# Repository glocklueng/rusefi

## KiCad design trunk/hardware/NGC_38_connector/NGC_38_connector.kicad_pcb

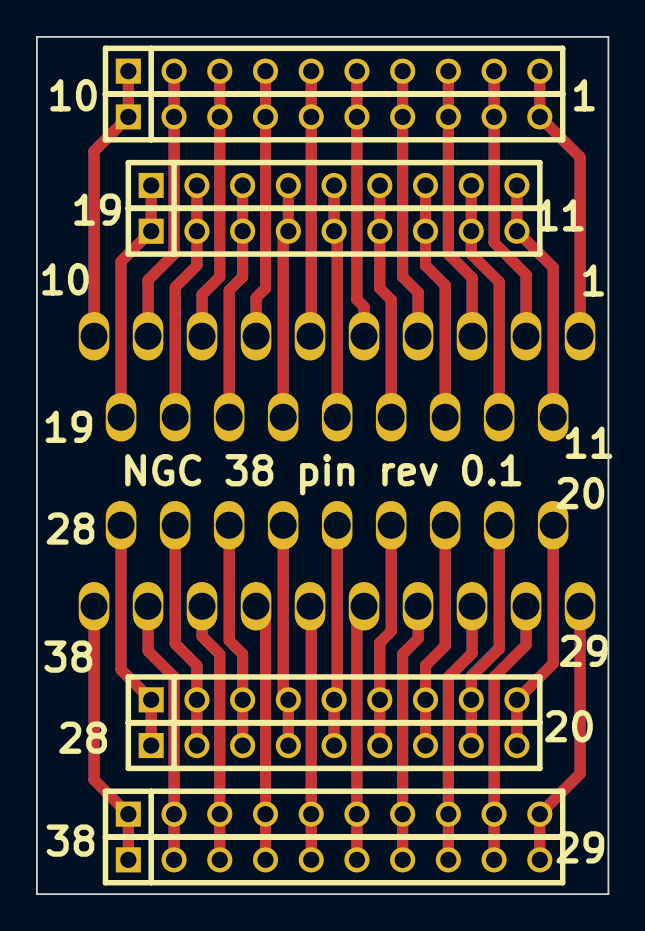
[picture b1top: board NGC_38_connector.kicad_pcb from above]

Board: 2 copper layers, 31.8 x 47.6 mm, 9 parts (0 on the bottom side), 38 nets.

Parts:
P1: DIL38; PCM_C1
P2, P4, P6, P9: CONN_10; SIL-10
P3, P5, P7, P8: CONN_9; SIL-9

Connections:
unnamed: P1.1, P2.1, P6.1
unnamed: P1.2, P2.2, P6.2
unnamed: P1.3, P2.3, P6.3
unnamed: P1.4, P2.4, P6.4
unnamed: P1.5, P2.5, P6.5
unnamed: P1.6, P2.6, P6.6
unnamed: P1.7, P2.7, P6.7
unnamed: P1.8, P2.8, P6.8
unnamed: P1.9, P2.9, P6.9
unnamed: P1.10, P2.10, P6.10
unnamed: P1.17, P3.7, P7.7
unnamed: P1.24, P5.5, P8.5
unnamed: P1.25, P5.6, P8.6
unnamed: P1.26, P5.7, P8.7
unnamed: P1.27, P5.8, P8.8
unnamed: P1.28, P5.9, P8.9
unnamed: P1.11, P3.1, P7.1
unnamed: P1.12, P3.2, P7.2
unnamed: P1.13, P3.3, P7.3
unnamed: P1.14, P3.4, P7.4
unnamed: P1.15, P3.5, P7.5
unnamed: P1.16, P3.6, P7.6
unnamed: P1.23, P5.4, P8.4
unnamed: P1.18, P3.8, P7.8
unnamed: P1.19, P3.9, P7.9
unnamed: P1.31, P4.3, P9.3
unnamed: P1.29, P4.1, P9.1
unnamed: P1.30, P4.2, P9.2
unnamed: P1.32, P4.4, P9.4
unnamed: P1.33, P4.5, P9.5
unnamed: P1.34, P4.6, P9.6
unnamed: P1.35, P4.7, P9.7
unnamed: P1.36, P4.8, P9.8
unnamed: P1.37, P4.9, P9.9
unnamed: P1.38, P4.10, P9.10
unnamed: P1.20, P5.1, P8.1
unnamed: P1.21, P5.2, P8.2
unnamed: P1.22, P5.3, P8.3

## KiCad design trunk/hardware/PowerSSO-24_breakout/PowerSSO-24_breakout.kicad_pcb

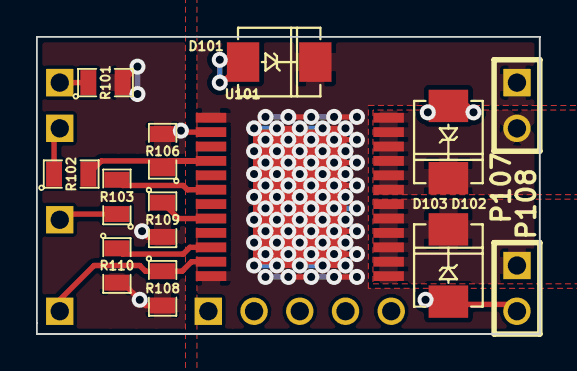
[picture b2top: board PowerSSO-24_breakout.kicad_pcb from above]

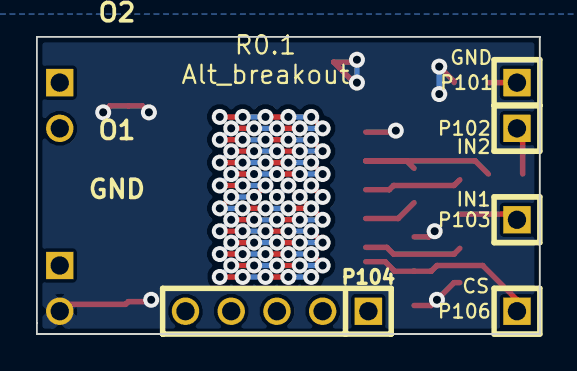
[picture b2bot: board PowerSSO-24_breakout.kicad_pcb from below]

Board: 2 copper layers, 27.9 x 16.5 mm, 18 parts (5 on the bottom side), 12 nets.

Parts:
D101, D102, D103: P6SMB36AT3G; DO-214AA(SMB)
P101, P102, P103, P106: CONN_1; SIL-1
P104: CONN_5; SIL-5
P107, P108: CONN_2; SIL-2
R101: TBD; SM0805
R102, R103, R106, R108: 10K; SM0805
R109, R110: 1K; SM0805
U101: VND5E025AKTR; PowerSSO-24

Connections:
/CS_DIS: P106.1, R108.1, U101.11
/I1: R109.1, U101.8
/I2: R110.1, U101.10
/IN1: R103.2, U101.6
/IN2: R102.2, R106.1, U101.4
/O1: D103.2, P108.1, U101.13, U101.14, U101.15, U101.16, U101.17, U101.18
/O2: D102.2, P107.2, U101.19, U101.20, U101.21, U101.22, U101.23, U101.24
/VCC: D101.2, P107.1, U101.1, U101.12, U101.EXP
GND: D101.1, D102.1, D103.1, P108.2, R101.2, R106.2, R108.2, R109.2, R110.2, U101.2
unnamed: P101.1, R101.1
unnamed: P103.1, R103.1
unnamed: P102.1, R102.1

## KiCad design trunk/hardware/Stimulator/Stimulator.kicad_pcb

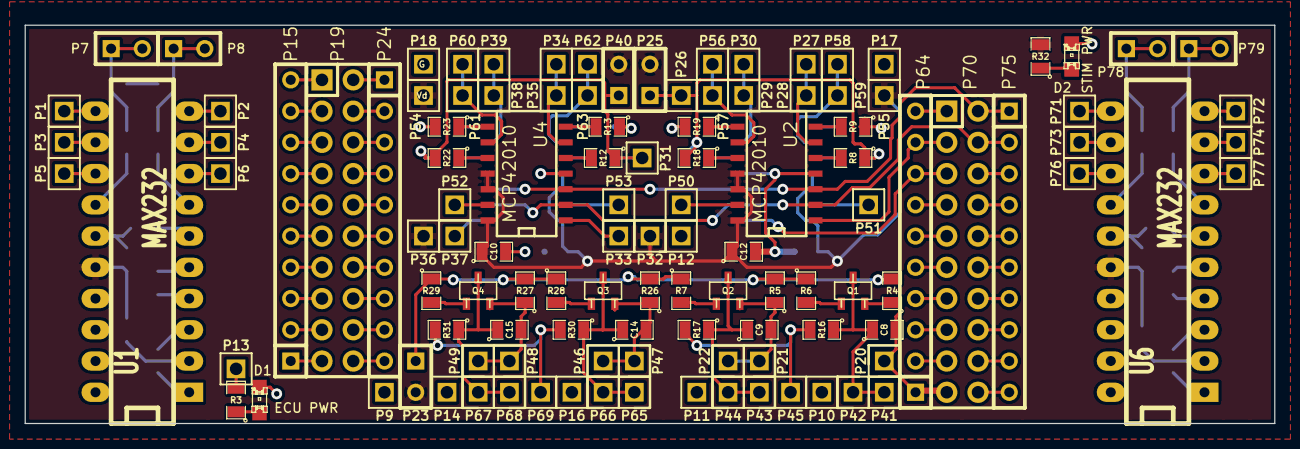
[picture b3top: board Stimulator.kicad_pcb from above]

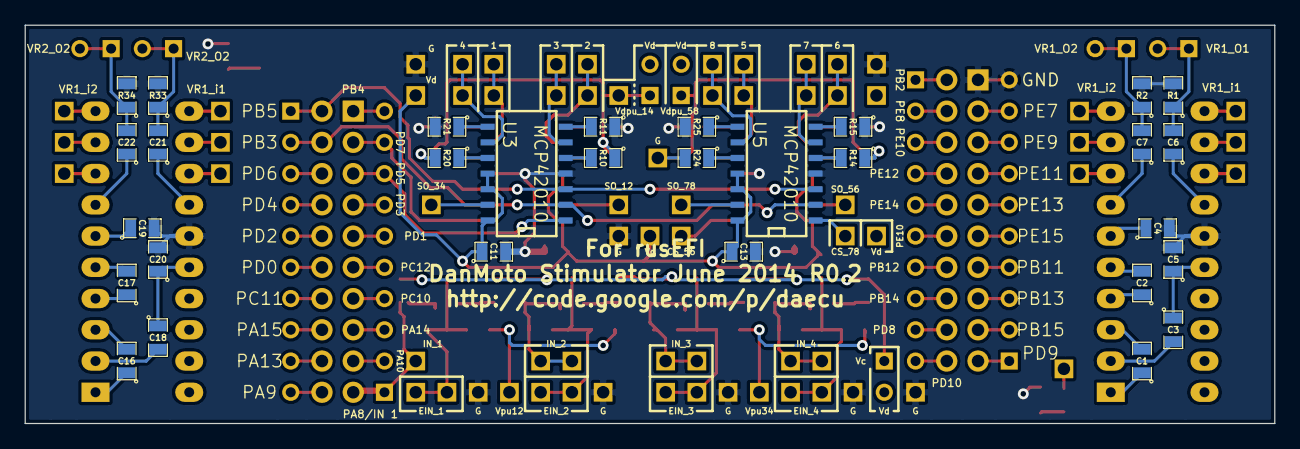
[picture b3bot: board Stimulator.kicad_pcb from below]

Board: 2 copper layers, 101.6 x 32.4 mm, 147 parts (30 on the bottom side), 122 nets.

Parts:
C1, C2, C3, C4, C5, C6, C7, C16, C17, C18, C19, C20, C21, C22: 1uF; SM0805
C8, C9, C14, C15: 100 pF; SM0805
C10, C11, C12, C13: 0.1uF; SM0805
D1: ECU PWR; LED-0805
D2: STIM PWR; LED-0805
P1, P2, P3, P4, P5, P6, P9, P10, P11, P12, P13, P14, P16, P17, P18, P20, P21, P22, P26, P27, P28, P29, P30, P31, P32, P33, P34, P35, P36, P37, P38, P39, P41, P42, P43, P44, P45, P46, P47, P48, P49, P50, P51, P52, P53, P54, P55, P56, P57, P58, P59, P60, P61, P62, P63, P65, P66, P67, P68, P69, P71, P72, P73, P74, P76, P77: CONN_1; PIN_ARRAY_1
P7, P8, P23, P25, P40, P78, P79: TEST; SIL-2
P15, P24, P64, P75: CONN_10; SIL-10
P19, P70: CONN_10X2; Pin_Header_Straight_2x10
Q1, Q2, Q3, Q4: 2N7002; sot23
R1, R2, R4, R5, R6, R7, R16, R17, R26, R27, R28, R29, R30, R31, R33, R34: 10k; SM0805
R3, R32: 700R; SM0805
R8, R9, R10, R11, R12, R13, R14, R15, R18, R19, R20, R21, R22, R23, R24, R25: 0; SM0805
U1, U6: MAX232; DIP-20__300_ELL
U2, U3, U4, U5: MCP42010; SO14N

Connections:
/CS_12: P64.9, P70.3, U2.1
/CS_34: P64.8, P70.5, U3.1
/CS_56: P33.1, U4.1
/CS_78: P37.1, U5.1
/EIN_1: C8.1, P41.1, P42.1, Q1.2, R16.1
/EIN_2: C9.1, P43.1, P44.1, Q2.2, R17.1
/EIN_3: C14.1, P65.1, P66.1, Q3.2, R30.1
/EIN_4: C15.1, P67.1, P68.1, Q4.2, R31.1
/IN_1: C8.2, P20.1, P64.1, P70.19, Q1.3, R4.1
/IN_2: C9.2, P21.1, P22.1, Q2.3, R5.1
/IN_3: C14.2, P46.1, P47.1, Q3.3, R26.1
/IN_4: C15.2, P48.1, P49.1, Q4.3, R27.1
/MISO: P64.10, P70.1
/MOSI: P70.2, P75.1, U2.3, U3.3, U4.3, U5.3
/OUT1: P27.1, P28.1, U2.6
/OUT2: P56.1, P57.1, U2.9
/OUT3: P29.1, P30.1, U3.6
/OUT4: P58.1, P59.1, U3.9
/OUT5: P34.1, P35.1, U4.6
/OUT6: P60.1, P61.1, U4.9
/OUT7: P38.1, P39.1, U5.6
/OUT8: P62.1, P63.1, U5.9
/SCK: P70.4, P75.2, U2.2, U3.2, U4.2, U5.2
/VR1-O1: C6.2, P7.1, P7.2, R1.1
/VR1-O2: C7.2, P8.1, P8.2, R2.1
/VR1_i1: P1.1, U1.11
/VR1_i2: P2.1, U1.10
/VR2-O1: C21.2, P78.1, P78.2, R33.1
/VR2-O2: C22.2, P79.1, P79.2, R34.1
/VR2_i1: P71.1, U6.11
/VR2_i2: P72.1, U6.10
/Vc: P23.1, R4.2, R5.2, R6.1, R7.1, R26.2, R27.2, R28.1, R29.1
/Vd: C3.1, C5.1, C10.1, C11.1, C12.1, C13.1, C18.1, C20.1, P23.2, P25.2, P32.1, P36.1, P40.2, P54.1, P55.1, R32.2, U1.16, U2.11, U2.12, U2.14, U3.11, U3.12, U3.14, U4.11, U4.12, U4.14, U5.11, U5.12, U5.14, U6.16
/Vdpu_14: P25.1, P26.1, R8.1, R10.1, R18.2, R20.2
/Vdpu_58: P31.1, P40.1, R12.1, R14.1, R22.2, R24.2
/Vipu12: P45.1, R16.2, R17.2
/Vipu34: P69.1, R30.2, R31.2
GND: C4.2, C5.2, C10.2, C11.2, C12.2, C13.2, C19.2, C20.2, D1.2, D2.2, P9.1, P10.1, P11.1, P12.1, P14.1, P15.10, P16.1, P17.1, P18.1, P19.1, R1.2, R2.2, R9.1, R11.1, R13.1, R15.1, R19.2, R21.2, R23.2, R25.2, R33.2, R34.2, U1.15, U2.4, U3.4, U4.4, U5.4, U6.15
unnamed: P53.1, U5.13
unnamed: P70.16, P75.8
unnamed: P15.6, P19.9
unnamed: P15.7, P19.7
unnamed: P15.8, P19.5
unnamed: P15.9, P19.3
unnamed: P70.6, P75.3
unnamed: P70.8, P75.4
unnamed: P70.10, P75.5
unnamed: P70.12, P75.6
unnamed: P70.14, P75.7
unnamed: P15.5, P19.11
unnamed: P70.18, P75.9
unnamed: P70.20, P75.10
unnamed: P64.2, P70.17
unnamed: P64.3, P70.15
unnamed: P64.4, P70.13
unnamed: P64.5, P70.11
unnamed: P64.6, P70.9
unnamed: P64.7, P70.7
unnamed: P19.6, P24.3
unnamed: P19.2, P24.1
unnamed: P19.4, P24.2
unnamed: P19.8, P24.4
unnamed: P19.10, P24.5
unnamed: P19.12, P24.6
unnamed: P19.14, P24.7
unnamed: P19.16, P24.8
unnamed: P19.18, P24.9
unnamed: P19.20, P24.10
unnamed: P15.1, P19.19
unnamed: P15.2, P19.17
unnamed: P15.3, P19.15
unnamed: P15.4, P19.13
unnamed: R14.2, U5.5
unnamed: R15.2, U5.7
unnamed: R25.1, U5.8
unnamed: R24.1, U5.10
unnamed: P50.1, U2.13
unnamed: P52.1, U4.13
unnamed: P51.1, U3.13
unnamed: C16.1, U6.1
unnamed: C16.2, U6.3
unnamed: C17.1, U6.4
unnamed: C17.2, U6.5
unnamed: C18.2, U6.2
unnamed: C19.1, U6.6
unnamed: P77.1, U6.8
unnamed: P76.1, U6.13
unnamed: D2.1, R32.1
unnamed: P13.1, R3.2
unnamed: C22.1, U6.7
unnamed: P74.1, U6.9
unnamed: P73.1, U6.12
unnamed: C21.1, U6.14
unnamed: P3.1, U1.12
unnamed: P4.1, U1.9
unnamed: C7.1, U1.7
unnamed: C1.1, U1.1
unnamed: C3.2, U1.2
unnamed: C1.2, U1.3
unnamed: C2.1, U1.4
unnamed: C2.2, U1.5
unnamed: C4.1, U1.6
unnamed: P6.1, U1.8
unnamed: P5.1, U1.13
unnamed: C6.1, U1.14
unnamed: D1.1, R3.1
unnamed: Q1.1, R6.2
unnamed: R8.2, U2.5
unnamed: R9.2, U2.7
unnamed: R19.1, U2.8
unnamed: R18.1, U2.10
unnamed: Q2.1, R7.2
unnamed: Q3.1, R28.2
unnamed: Q4.1, R29.2
unnamed: R13.2, U4.7
unnamed: R23.1, U4.8
unnamed: R22.1, U4.10
unnamed: R10.2, U3.5
unnamed: R11.2, U3.7
unnamed: R21.1, U3.8
unnamed: R20.1, U3.10
unnamed: R12.2, U4.5

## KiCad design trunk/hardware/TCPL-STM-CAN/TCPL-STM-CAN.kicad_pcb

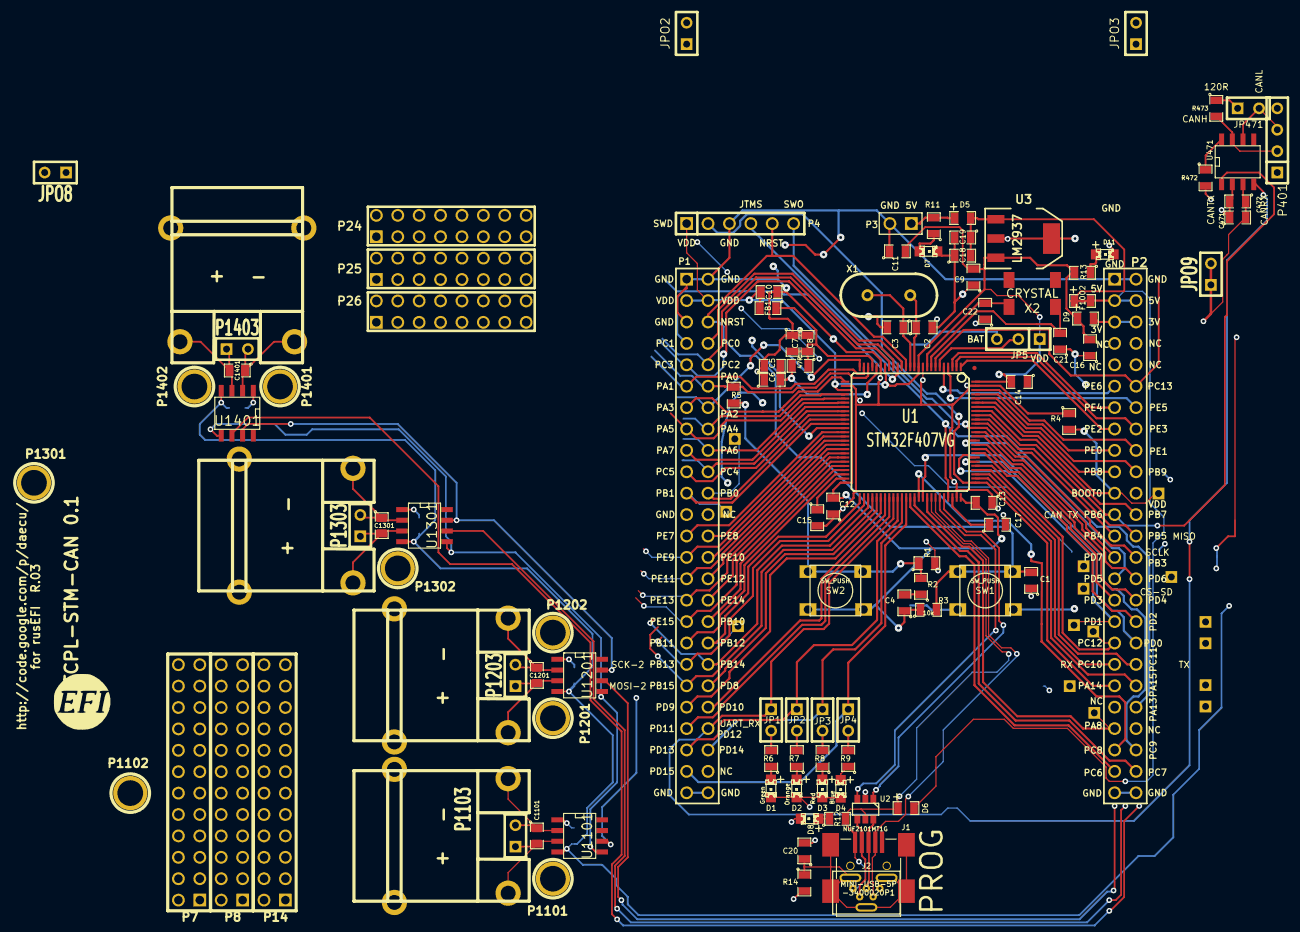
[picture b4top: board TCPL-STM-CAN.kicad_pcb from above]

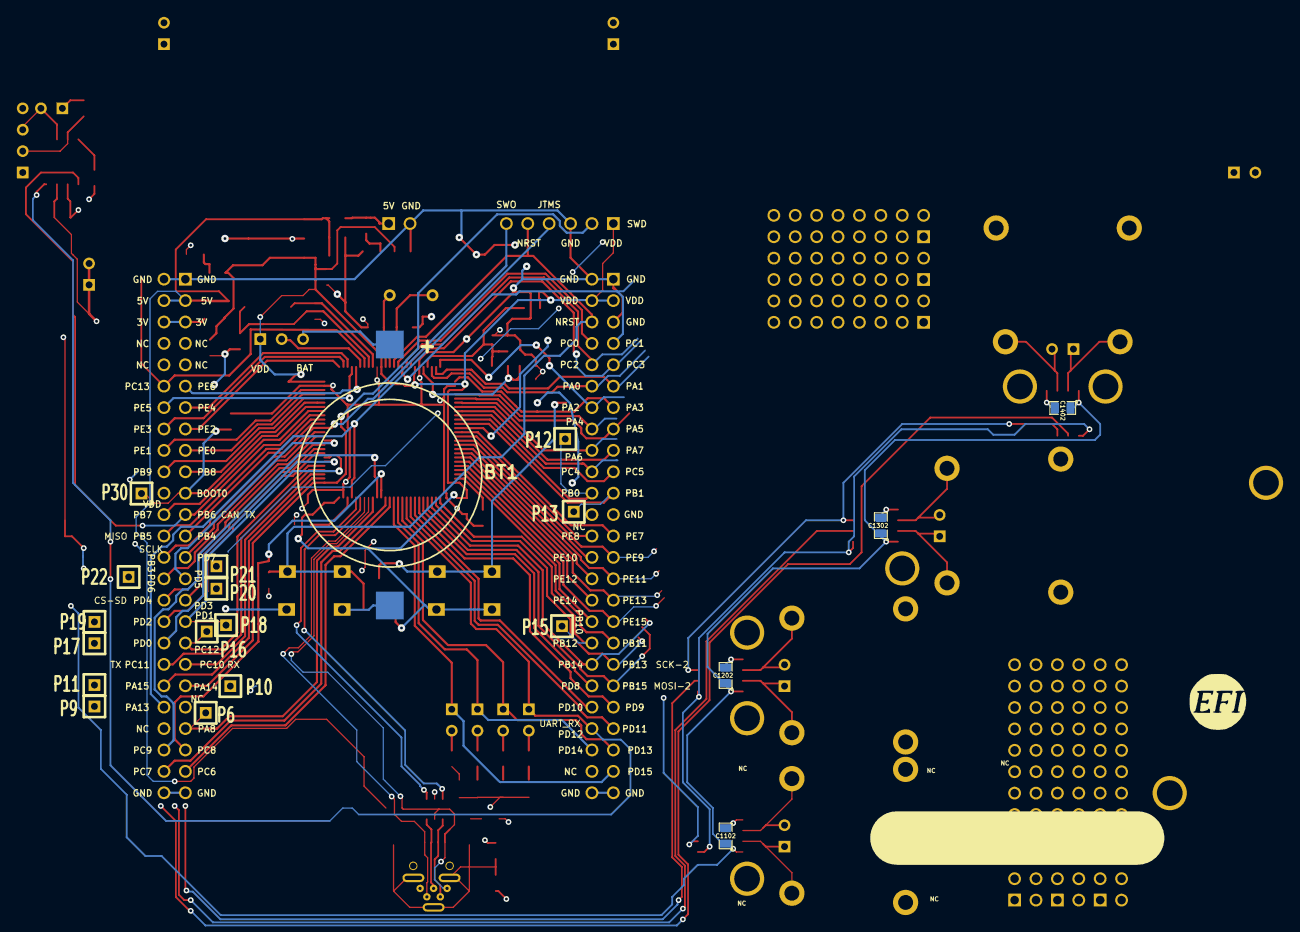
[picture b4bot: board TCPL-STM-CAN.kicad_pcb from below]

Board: 4 copper layers, 129 parts (21 on the bottom side), 124 nets.

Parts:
BT1: BATTERY_CR2032; BATT_CR2032_MPD
C1, C5, C8: 0.01uF; SM0805
C2, C3: 20pF; SM0805
C4, C15, C17: 2u2F; SM0805
C6, C7, C16: 1uF; SM0805
C9, C10, C11, C12, C13, C14, C18, C20, C471: 0.1uF; SM0805
C19, C472: 4.7uF; SM0805
C21, C22: 12.5pF; SM0805
C1101, C1201, C1301, C1401: 10nF; SM0805-SM0603
C1102, C1202, C1302, C1402: 100nF; SM0805-SM0603
D1, D7, D8, D11: LED-grn; LED-0805_A
D2: LED-org; LED-0805_A
D3: LED-red; LED-0805_A
D4: LED-blu; LED-0805_A
D5, D6, D9: DIODESCH; SM0805-diode
F1002: FUSE; SM0805-diode
FB1: FILTER; SM0805
G1: LOGO; LOGO_F
G2: LOGO
J1: MINI-USB-5P-3400020P1
J2: MINI-USB-5P-3400020P1V; MINI-USB_RCTP_V-T_B
JP1, JP2, JP3, JP4, JP471: JUMPER; JUMPER-2
JP5: JUMPER3; SIL-3
JPO2, JPO3, JPO8, JPO9: TEST-gnd; SIL-2
P1, P2: CONN_25X2; PIN_ARRAY_25x2_A
P3: CONN_2; PIN_ARRAY_2_A
P4: CONN_6; PIN_ARRAY-6X1
P6, P9, P10, P11, P12, P13, P15, P16, P17, P18, P19, P20, P21, P22, P30: CONN_1; SIL-1
P7, P8, P14: CONN_12X2; pin_array_12x2
P24, P25, P26: CONN_8X2; pin_array_8x2
P401: CONN_4; SIL-4
P1101, P1102, P1201, P1202, P1301, P1302, P1401, P1402: CONN_1; 1pin
P1103, P1203, P1303, P1403: CONN_2; SIL-2
P1104, P1204, P1304, P1404: CONN_2; tcpl_PCC-SMP
R1, R3, R4, R472: 10k; SM0805
R2: 100R; SM0805
R5: 330R; SM0805
R6, R7, R8, R9: 680R; SM0805
R10: 47R; SM0805
R11, R12, R13: 1k; SM0805
R14: 100k; SM0805
R473: 120; SM0805
SW1, SW2: SW_PUSH; TL-1105
U1: STM32F407VG; TQFP_100
U2: NUF2101MT1G; SOT-457
U3: LM2937; SOT223
U471: SN65HVD230; SO8E
U1101, U1201, U1301, U1401: MAX31855KASA; SO8E
X1: CRYSTAL; HC-49V
X2: CRYSTAL; MC-306

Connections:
/can_brd_1/3.3V: C471.2, C472.1, C1102.1, C1202.1, C1302.1, C1402.1, D9.2, JPO9.1, JPO9.2, P2.5, P2.6, U471.3, U1101.4, U1201.4, U1301.4, U1401.4
/can_brd_1/5V: C18.2, C19.1, D5.2, D6.2, F1002.1, F1002.2, JPO8.1, JPO8.2, P2.3, P2.4, P401.1, U3.1
/can_brd_1/CANH: P401.2, R473.2, U471.7
/can_brd_1/CANL: JP471.2, P401.3, U471.6
/can_brd_1/CAN_RX: JP1.1, P1.44, U1.59, U471.4
/can_brd_1/CAN_TX: P2.23, U1.92, U471.1
/stm32f407_board/BOOT0: P2.21, P30.1, R4.2, U1.94
/stm32f407_board/D+: J1.3, J2.3, U2.6
/stm32f407_board/D-: J1.2, J2.2, U2.4
/stm32f407_board/NRST: C1.2, P1.6, P4.5, R3.2, SW1.1, U1.14
/stm32f407_board/PA0: P1.12, R5.1, U1.23
/stm32f407_board/PA1: P1.11, U1.24
/stm32f407_board/PA2: P1.14, U1.25
/stm32f407_board/PA3: P1.13, U1.26
/stm32f407_board/PA4: P1.16, U1.29
/stm32f407_board/PA5: P1.15, U1.30
/stm32f407_board/PA6: P1.18, U1.31
/stm32f407_board/PA7: P1.17, U1.32
/stm32f407_board/PA9: D6.1, J1.1, J2.1, R12.2, U1.68, U2.5
/stm32f407_board/PA10: J1.4, J2.4, U1.69
/stm32f407_board/PA11: U1.70, U2.3
/stm32f407_board/PA12: U1.71, U2.1
/stm32f407_board/PA15: P2.40, P11.1, U1.77
/stm32f407_board/PB0: P1.22, P12.1, U1.35
/stm32f407_board/PB1: P1.21, P13.1, U1.36
/stm32f407_board/PB3: P2.28, P4.6, U1.89
/stm32f407_board/PB4: P2.25, U1.90
/stm32f407_board/PB5: P2.26, U1.91
/stm32f407_board/PB7: P2.24, U1.93
/stm32f407_board/PB8: P2.19, U1.95
/stm32f407_board/PB9: P2.20, U1.96
/stm32f407_board/PB10: P1.34, U1.47
/stm32f407_board/PB11: P1.35, U1.48
/stm32f407_board/PB13: P1.37, U1.52
/stm32f407_board/PB14: P1.38, U1.53
/stm32f407_board/PB15: P1.39, U1.54
/stm32f407_board/PC0: P1.8, U1.15
/stm32f407_board/PC1: P1.7, U1.16
/stm32f407_board/PC2: P1.10, U1.17
/stm32f407_board/PC3: P1.9, U1.18
/stm32f407_board/PC4: P1.20, U1.33
/stm32f407_board/PC5: P1.19, U1.34
/stm32f407_board/PC6: P2.47, U1.63
/stm32f407_board/PC7: P2.48, U1.64
/stm32f407_board/PC8: P2.45, U1.65
/stm32f407_board/PC9: P2.46, U1.66
/stm32f407_board/PC10: P2.37, U1.78
/stm32f407_board/PC11: P2.38, U1.79
/stm32f407_board/PC12: P2.35, P16.1, U1.80
/stm32f407_board/PC13: P2.12, U1.7
/stm32f407_board/PD0: P2.36, P17.1, U1.81
/stm32f407_board/PD1: P2.33, P18.1, U1.82
/stm32f407_board/PD2: P2.34, P19.1, U1.83
/stm32f407_board/PD3: P2.31, P20.1, U1.84
/stm32f407_board/PD4: P2.32, U1.85
/stm32f407_board/PD5: P2.29, P21.1, U1.86
/stm32f407_board/PD6: P2.30, P22.1, U1.87
/stm32f407_board/PD7: P2.27, U1.88
/stm32f407_board/PD8: P1.40, U1.55
/stm32f407_board/PD9: P1.41, U1.56
/stm32f407_board/PD10: P1.42, U1.57
/stm32f407_board/PD11: P1.43, U1.58
/stm32f407_board/PD13: JP2.1, P1.45, U1.60
/stm32f407_board/PD14: JP3.1, P1.46, U1.61
/stm32f407_board/PD15: JP4.1, P1.47, U1.62
/stm32f407_board/PE0: P2.17, U1.97
/stm32f407_board/PE1: P2.18, U1.98
/stm32f407_board/PE2: P2.15, U1.1
/stm32f407_board/PE3: P2.16, U1.2
/stm32f407_board/PE4: P2.13, U1.3
/stm32f407_board/PE5: P2.14, U1.4
/stm32f407_board/PE6: P2.11, U1.5
/stm32f407_board/PE7: P1.25, U1.38
/stm32f407_board/PE8: P1.26, U1.39
/stm32f407_board/PE9: P1.27, U1.40
/stm32f407_board/PE10: P1.28, U1.41
/stm32f407_board/PE11: P1.29, U1.42
/stm32f407_board/PE12: P1.30, U1.43
/stm32f407_board/PE13: P1.31, U1.44
/stm32f407_board/PE14: P1.32, U1.45
/stm32f407_board/PE15: P1.33, U1.46
/stm32f407_board/VDD: C4.1, C9.2, C10.2, C11.2, C12.2, C13.2, C14.2, C16.2, D9.1, FB1.2, JP5.1, P1.3, P1.4, P4.1, R3.1, R13.2, SW2.2, U1.11, U1.19, U1.28, U1.50, U1.75, U1.100, U3.3
/stm32f407_board/shield: C20.1, J1.6, J2.6, R14.1
/thermocouple1//CS: P1.36, P15.1, U1.51, U1101.6
/thermocouple1/MISO: U1101.7, U1201.7, U1301.7, U1401.7
/thermocouple1/SCK: U1101.5, U1201.5, U1301.5, U1401.5
/thermocouple1/TCPL+: C1101.2, P1103.1, P1104.2, U1101.3
/thermocouple1/TCPL-: C1101.1, P1103.2, P1104.1, U1101.2
/thermocouple2//CS: P2.39, P4.2, P10.1, U1.76, U1201.6
/thermocouple2/TCPL+: C1201.2, P1203.1, P1204.2, U1201.3
/thermocouple2/TCPL-: C1201.1, P1203.2, P1204.1, U1201.2
/thermocouple3//CS: P2.43, P6.1, U1.67, U1301.6
/thermocouple3/TCPL+: C1301.2, P1303.1, P1304.2, U1301.3
/thermocouple3/TCPL-: C1301.1, P1303.2, P1304.1, U1301.2
/thermocouple4//CS: P2.42, P4.4, P9.1, U1.72, U1401.6
/thermocouple4/TCPL+: C1401.2, P1403.1, P1404.2, U1401.3
/thermocouple4/TCPL-: C1401.1, P1403.2, P1404.1, U1401.2
GND: BT1.2, C1.1, C2.2, C3.2, C5.1, C6.1, C7.1, C8.1, C9.1, C10.1, C11.1, C12.1, C13.1, C14.1, C15.2, C16.1, C17.2, C18.1, C19.2, C20.2, C21.1, C22.1, C471.1, C472.2, C1102.2, C1202.2, C1302.2, C1402.2, D1.2, D2.2, D3.2, D4.2, D7.2, D8.2, D11.2, J1.5, J2.5, JPO2.1, JPO2.2, JPO3.1, JPO3.2, P1.1, P1.2, P1.5, P1.23, P1.49, P1.50, P2.1, P2.2, P2.49, P2.50, P3.2, P4.3, P401.4, R1.2, R4.1, R14.2, R472.2, SW1.2, U1.10, U1.20, U1.27, U1.37, U1.74, U1.99, U2.2, U3.2, U3.4, U471.2, U1101.1, U1201.1, U1301.1, U1401.1
unnamed: R472.1, U471.8
unnamed: JP471.1, R473.1
unnamed: C22.2, U1.9, X2.1
unnamed: C21.2, U1.8, X2.2
unnamed: C2.1, U1.12, X1.2
unnamed: D2.1, R7.1
unnamed: D3.1, R8.1
unnamed: D4.1, R9.1
unnamed: D7.1, R11.1
unnamed: D8.1, R12.1
unnamed: D11.1, R13.1
unnamed: D1.1, R6.1
unnamed: D5.1, P3.1, R11.2
unnamed: BT1.1, JP5.3
unnamed: JP5.2, U1.6
unnamed: JP4.2, R9.2
unnamed: JP3.2, R8.2
unnamed: JP2.2, R7.2
unnamed: JP1.2, R6.2
unnamed: R1.1, R2.2, R5.2, SW2.1
unnamed: C5.2, C6.2, R10.2, U1.21
unnamed: C3.1, U1.13, X1.1
unnamed: C17.1, U1.73
unnamed: C15.1, U1.49
unnamed: C4.2, R2.1
unnamed: C7.2, C8.2, FB1.1, R10.1, U1.22

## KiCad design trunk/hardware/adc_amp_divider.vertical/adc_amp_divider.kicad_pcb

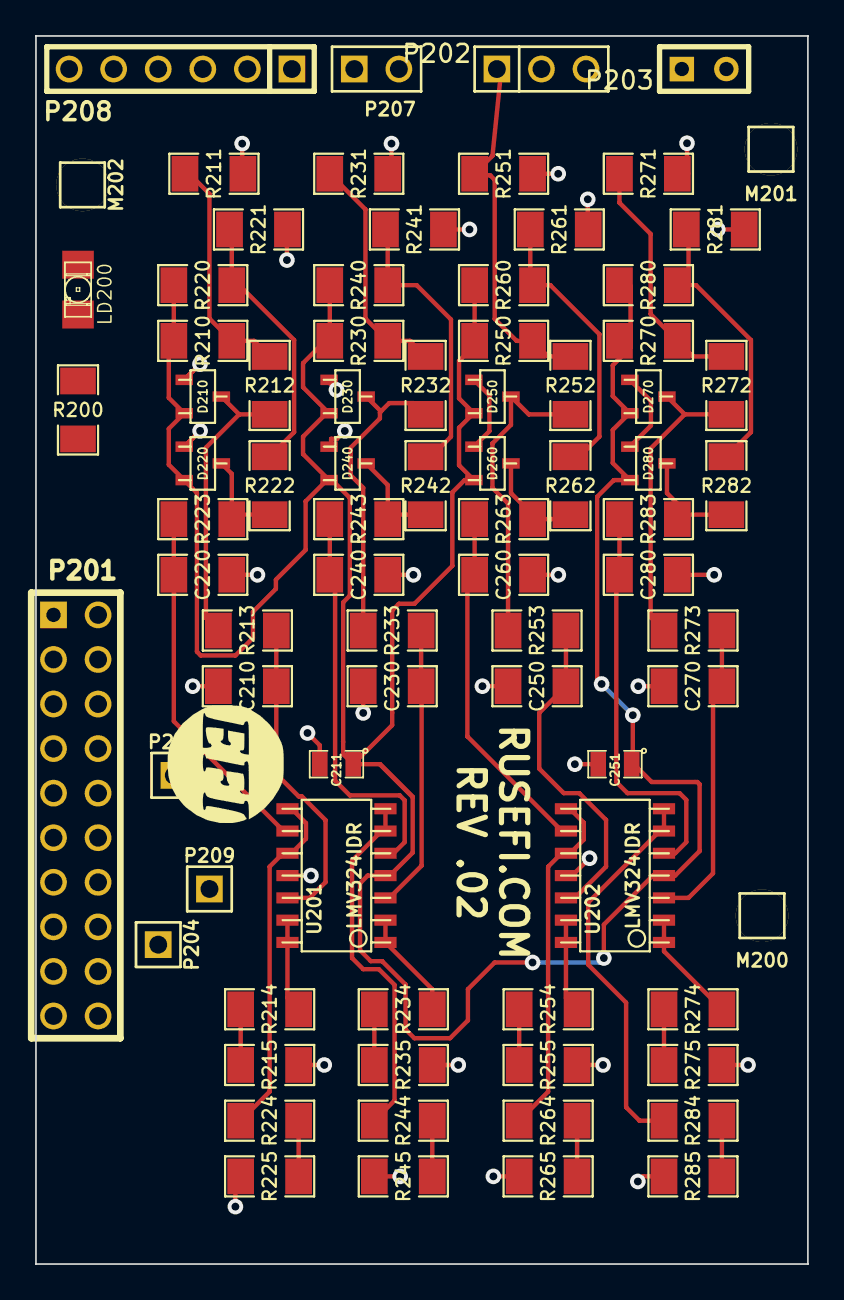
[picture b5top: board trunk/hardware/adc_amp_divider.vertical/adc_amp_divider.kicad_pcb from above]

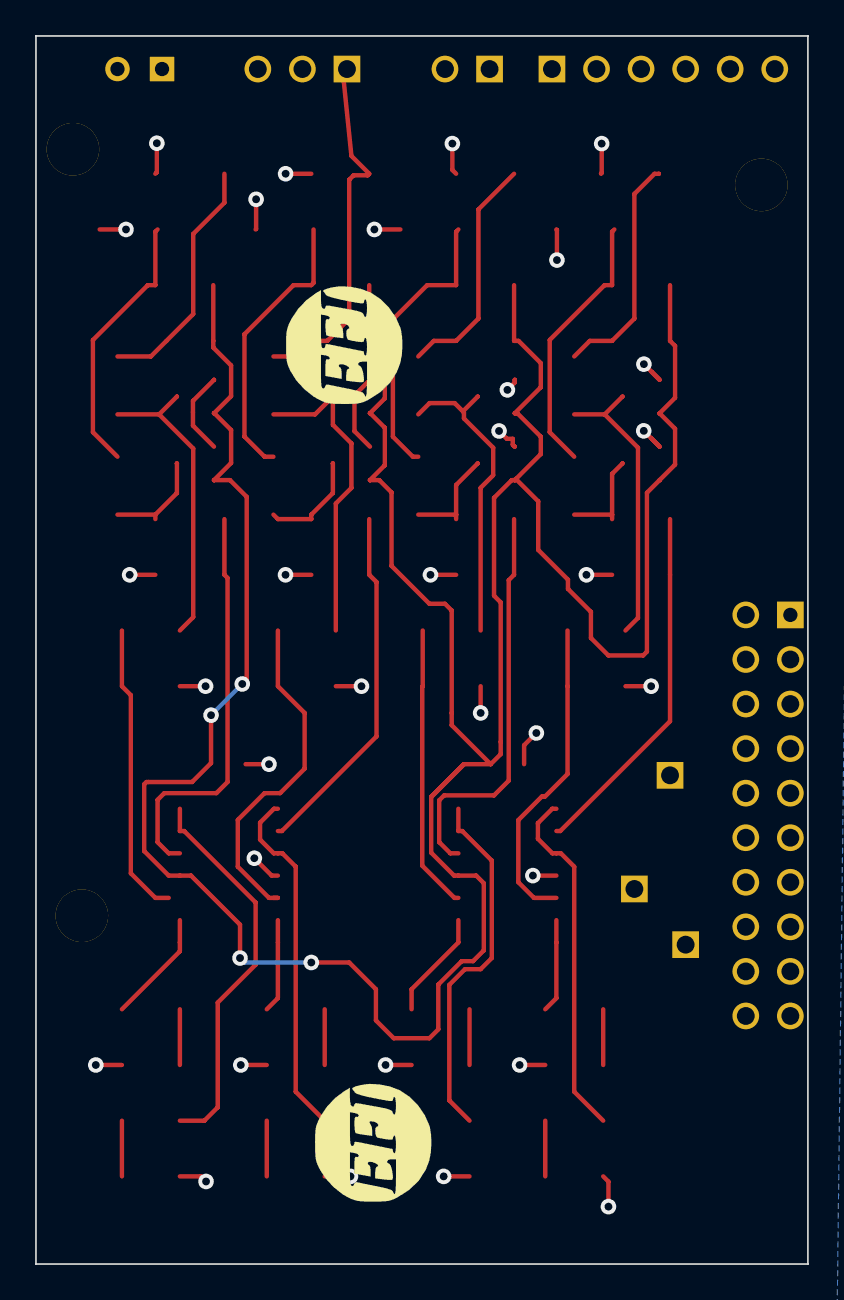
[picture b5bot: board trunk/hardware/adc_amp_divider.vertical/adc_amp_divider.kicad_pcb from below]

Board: 2 copper layers, 44.0 x 70.0 mm, 84 parts (2 on the bottom side), 46 nets.

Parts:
C210, C220, C230, C240, C250, C260, C270, C280: 0.01uF; SM1206
C211, C251: 0.1uF; SM0805
D210, D220, D230, D240, D250, D260, D270, D280: DOUBLE_SCHOTTKY; sot23
G200: LOGO
G201, G202: LOGO; LOGO_F
LD200: LED; LED-1206
M200, M201, M202: CONN_1; PIN_ARRAY_1
P201: CONN_10X2; PIN_ARRAY_10X2
P202: CONN_3; PIN_ARRAY_3X1
P203: CONN_2; SIL-2
P204, P205, P209: CONN_1; PIN_ARRAY_1
P207: CONN_2; PIN_ARRAY_2X1
P208: CONN_6; PIN_ARRAY-6X1
R200, R213, R223, R233, R243, R253, R263, R273, R283: 100; SM1206
R210, R220, R230, R240, R250, R260, R270, R280: 2700; SM1206
R211, R221, R231, R241, R251, R261, R271, R281: 500K; SM1206
R212, R222, R232, R242, R252, R262, R272, R282: 10k; SM1206
R214, R215, R224, R225, R234, R235, R244, R245, R254, R255, R264, R265, R274, R275, R284, R285: 1500; SM1206
U201, U202: LMV324IDR; so-14

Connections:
/INP1: P208.6, R210.1, R211.1, R212.1
/INP2: P208.5, R220.1, R221.1, R222.1
/INP3: P208.4, R230.1, R231.1, R232.1
/INP4: P208.3, R240.1, R241.1, R242.1
/INP5: P208.2, R250.1, R251.1, R252.1
/INP6: P208.1, R260.1, R261.1, R262.1
/INP7: P207.1, R270.1, R271.1, R272.1
/INP8: P207.2, R280.1, R281.1, R282.1
/OUT1: P201.19, R214.2, R215.1
/OUT2: P201.20, R224.2, R225.1
/OUT3: P201.17, R234.2, R235.1
/OUT4: P201.18, R244.2, R245.1
/OUT5: P201.14, R254.2, R255.1
/OUT6: P201.13, R264.2, R265.1
/OUT7: P201.12, R274.2, R275.1
/OUT8: P201.11, R284.2, R285.1
/PA4: P201.16, P209.1
/PA5: P201.15, P204.1
/PC0: P201.8, P205.1
GND: C210.1, C211.2, C220.1, C230.1, C240.1, C250.1, C251.2, C260.1, C270.1, C280.1, D210.1, D220.1, D230.1, D240.1, D250.1, D260.1, D270.1, D280.1, LD200.1, P201.1, P201.2, P201.5, P203.1, P203.2, R211.2, R215.2, R221.2, R225.2, R231.2, R235.2, R241.2, R245.2, R251.2, R255.2, R261.2, R265.2, R271.2, R275.2, R281.2, R285.2, U201.11, U202.11
unnamed: LD200.2, R200.2
unnamed: C260.2, R263.2, U202.9
unnamed: D210.2, R212.2, R213.1
unnamed: D220.2, R222.2, R223.1
unnamed: D240.2, R242.2, R243.1
unnamed: R284.1, U202.6, U202.7
unnamed: C240.2, R243.2, U201.5
unnamed: R274.1, U202.1, U202.2
unnamed: C230.2, R233.2, U201.3
unnamed: C270.2, R273.2, U202.3
unnamed: R234.1, U201.1, U201.2
unnamed: R244.1, U201.6, U201.7
unnamed: C250.2, R253.2, U202.12
unnamed: R264.1, U202.8, U202.10
unnamed: R254.1, U202.13, U202.14
unnamed: C280.2, R283.2, U202.5
unnamed: D260.2, R262.2, R263.1
unnamed: D250.2, R252.2, R253.1
unnamed: D280.2, R282.2, R283.1
unnamed: D270.2, R272.2, R273.1
unnamed: R214.1, U201.13, U201.14
unnamed: C210.2, R213.2, U201.12
unnamed: C220.2, R223.2, U201.9
unnamed: R224.1, U201.8, U201.10
unnamed: D230.2, R232.2, R233.1
VCC: C211.1, C251.1, D210.3, D220.3, D230.3, D240.3, D250.3, D260.3, D270.3, D280.3, P202.1, P202.2, P202.3, R200.1, R210.2, R220.2, R230.2, R240.2, R250.2, R260.2, R270.2, R280.2, U201.4, U202.4

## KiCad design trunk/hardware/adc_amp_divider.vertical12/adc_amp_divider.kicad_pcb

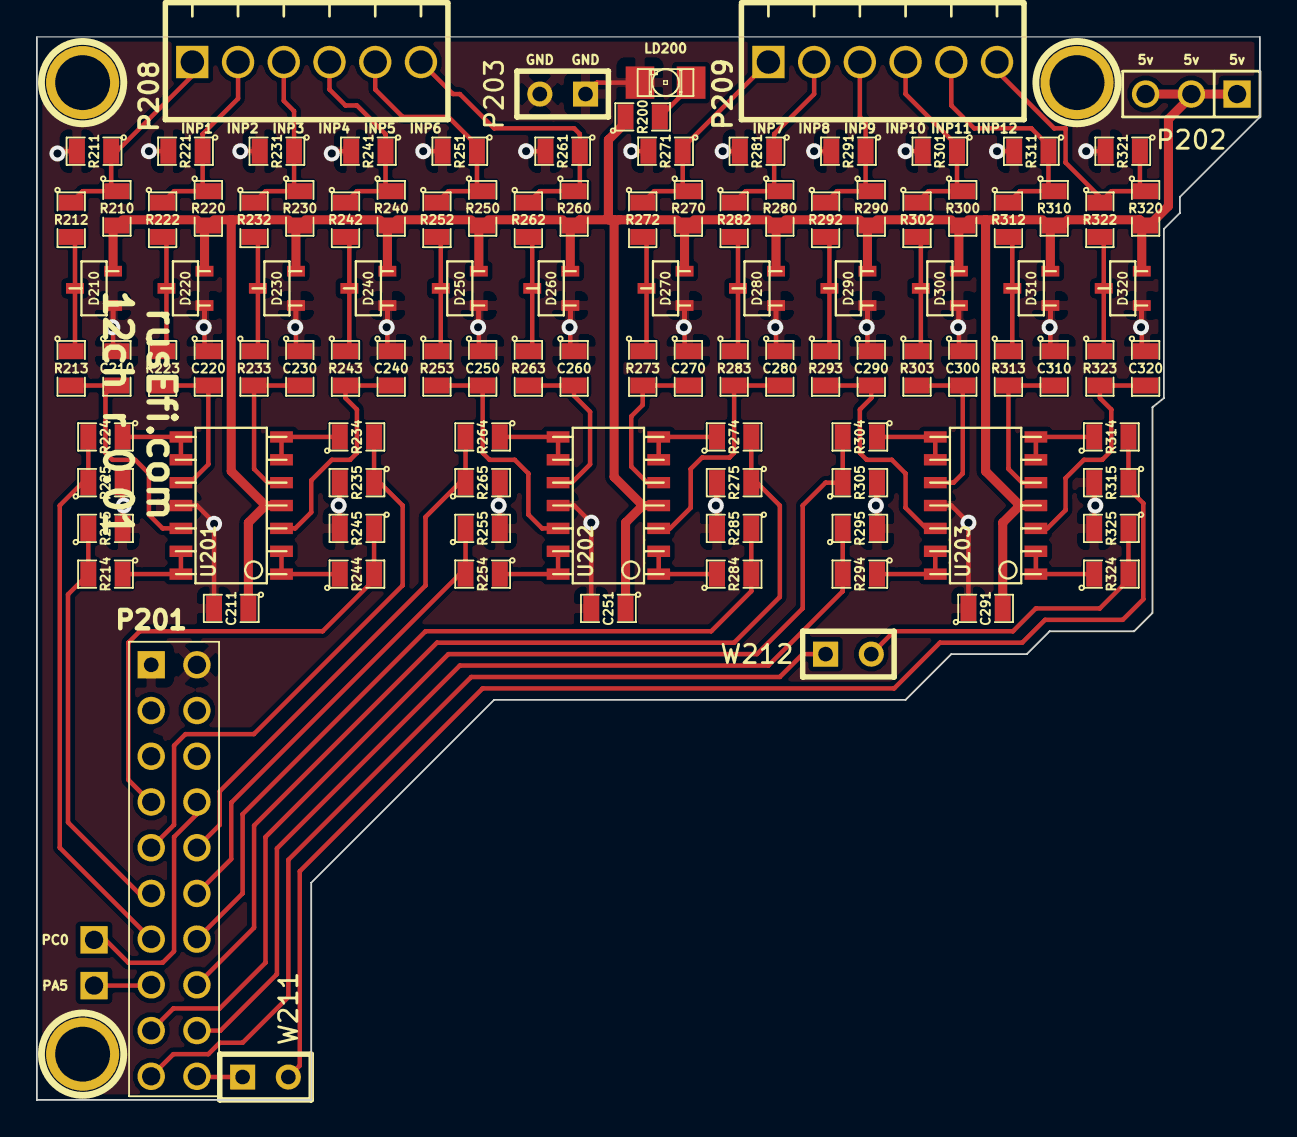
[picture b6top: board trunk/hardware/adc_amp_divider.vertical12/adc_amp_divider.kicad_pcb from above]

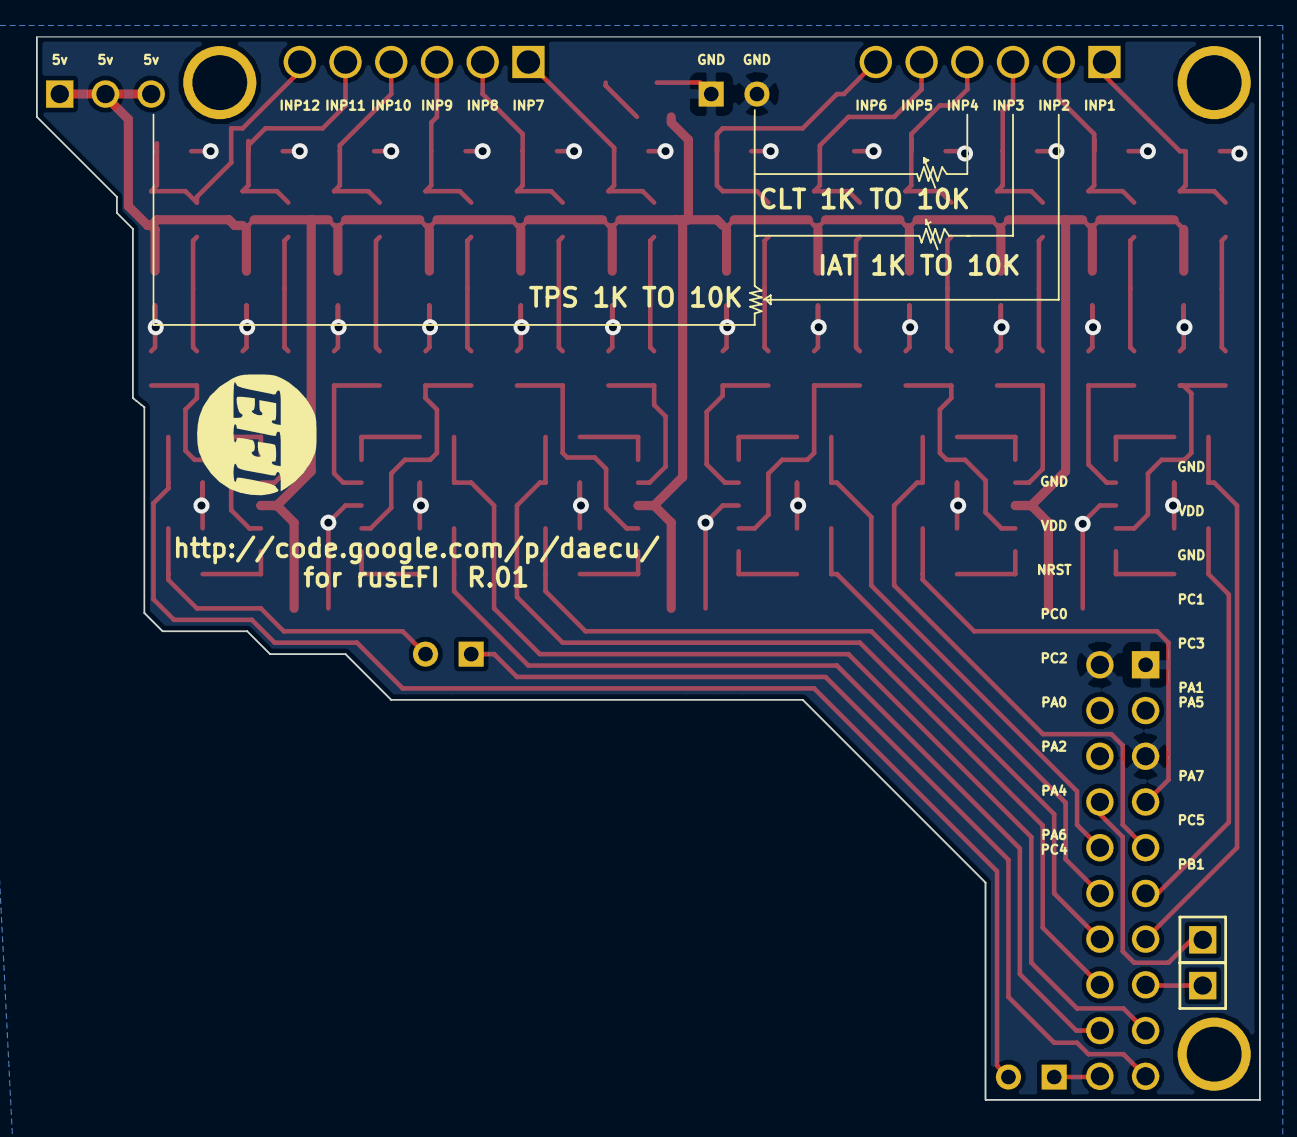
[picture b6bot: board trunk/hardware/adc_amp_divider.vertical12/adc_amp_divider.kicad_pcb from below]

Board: 2 copper layers, 67.9 x 59.1 mm, 117 parts (3 on the bottom side), 67 nets.

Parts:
C210, C220, C230, C240, C250, C260, C270, C280, C290, C300, C310, C320: 0.01uF; SM0805
C211, C251, C291: 0.1uF; SM0805
D210, D220, D230, D240, D250, D260, D270, D280, D290, D300, D310, D320: DOUBLE_SCHOTTKY; sot23
G201: LOGO; LOGO_F
LD200: LED; LED-1206
M200, M201, M202: CONN_1; 1pin
P201: CONN_10X2; PIN_ARRAY_10X2_M
P202: CONN_3; PIN_ARRAY_3X1
P203: CONN_2; SIL-2
P204, P205: CONN_1; PIN_ARRAY_1
P208, P209: CONN_6; 6_screw_term_.1in
R200, R213, R223, R233, R243, R253, R263, R273, R283, R293, R303, R313, R323: 100; SM0805
R210, R220, R230, R240, R250, R260, R270, R280, R290, R300, R310, R320: 2700; SM0805
R211, R221, R231, R241, R251, R261, R271, R281, R291, R301, R311, R321: 500K; SM0805
R212, R222, R232, R242, R252, R262, R272, R282, R292, R302, R312, R322: 10k; SM0805
R214, R215, R224, R225, R234, R235, R244, R245, R254, R255, R264, R265, R274, R275, R284, R285, R294, R295, R304, R305, R314, R315, R324, R325: 1500; SM0805
U201, U202, U203: LMV324IDR; so-14
W211, W212: TEST; SIL-2

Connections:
/5V: C211.1, C251.1, C291.2, D210.3, D220.3, D230.3, D240.3, D250.3, D260.3, D270.3, D280.3, D290.3, D300.3, D310.3, D320.3, P202.1, P202.2, P202.3, R200.1, R210.2, R220.2, R230.2, R240.2, R250.2, R260.2, R270.2, R280.2, R290.2, R300.2, R310.2, R320.2, U201.4, U202.4, U203.4
/INP1: P208.1, R210.1, R211.1, R212.1
/INP2: P208.2, R220.1, R221.1, R222.1
/INP3: P208.3, R230.1, R231.1, R232.1
/INP4: P208.4, R240.1, R241.1, R242.1
/INP5: P208.5, R250.1, R251.1, R252.1
/INP6: P208.6, R260.1, R261.1, R262.1
/INP7: P209.1, R270.1, R271.1, R272.1
/INP8: P209.2, R280.1, R281.1, R282.1
/INP9: P209.3, R290.1, R291.1, R292.1
/INP10: P209.4, R300.1, R301.1, R302.1
/INP11: P209.5, R310.1, R311.1, R312.1
/INP12: P209.6, R320.1, R321.1, R322.1
/OUT1: P201.11, R214.2, R215.1
/OUT2: P201.13, R224.2, R225.1
/OUT3: P201.9, R234.2, R235.1
/OUT4: P201.7, R244.2, R245.1
/OUT5: P201.12, R254.2, R255.1
/OUT6: P201.10, R264.2, R265.1
/OUT7: P201.16, R274.2, R275.1
/OUT8: P201.14, R284.2, R285.1
/OUT9: P201.18, R294.2, R295.1
/OUT10: P201.17, R304.2, R305.1
/OUT11: P201.20, W211.1
/OUT12: P201.19, W212.1
/PA5: P201.15, P204.1
/PC0: P201.8, P205.1
GND: C210.1, C211.2, C220.1, C230.1, C240.1, C250.1, C251.2, C260.1, C270.1, C280.1, C290.1, C291.1, C300.1, C310.1, C320.1, D210.1, D220.1, D230.1, D240.1, D250.1, D260.1, D270.1, D280.1, D290.1, D300.1, D310.1, D320.1, LD200.2, P201.1, P201.2, P201.5, P203.1, P203.2, R211.2, R215.2, R221.2, R225.2, R231.2, R235.2, R241.2, R245.2, R251.2, R255.2, R261.2, R265.2, R271.2, R275.2, R281.2, R285.2, R291.2, R295.2, R301.2, R305.2, R311.2, R315.2, R321.2, R325.2, U201.11, U202.11, U203.11
unnamed: D250.2, R252.2, R253.1
unnamed: D260.2, R262.2, R263.1
unnamed: D210.2, R212.2, R213.1
unnamed: D220.2, R222.2, R223.1
unnamed: D280.2, R282.2, R283.1
unnamed: R214.1, U201.13, U201.14
unnamed: R224.1, U201.8, U201.9
unnamed: D270.2, R272.2, R273.1
unnamed: R244.1, U201.1, U201.2
unnamed: D300.2, R302.2, R303.1
unnamed: D290.2, R292.2, R293.1
unnamed: R304.1, U203.8, U203.9
unnamed: R294.1, U203.13, U203.14
unnamed: C290.2, R293.2, U203.12
unnamed: C300.2, R303.2, U203.10
unnamed: R314.1, U203.6, U203.7
unnamed: R324.1, U203.1, U203.2
unnamed: C310.2, R313.2, U203.5
unnamed: C320.2, R323.2, U203.3
unnamed: D320.2, R322.2, R323.1
unnamed: D310.2, R312.2, R313.1
unnamed: R324.2, R325.1, W212.2
unnamed: R314.2, R315.1, W211.2
unnamed: C250.2, R253.2, U202.12
unnamed: R254.1, U202.13, U202.14
unnamed: R274.1, U202.6, U202.7
unnamed: R264.1, U202.8, U202.9
unnamed: C240.2, R243.2, U201.3
unnamed: C230.2, R233.2, U201.5
unnamed: C270.2, R273.2, U202.5
unnamed: C280.2, R283.2, U202.3
unnamed: C220.2, R223.2, U201.10
unnamed: C210.2, R213.2, U201.12
unnamed: C260.2, R263.2, U202.10
unnamed: R284.1, U202.1, U202.2
unnamed: D240.2, R242.2, R243.1
unnamed: LD200.1, R200.2
unnamed: D230.2, R232.2, R233.1
unnamed: R234.1, U201.6, U201.7
